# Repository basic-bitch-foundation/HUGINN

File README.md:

# HUGINN
 Introduction
--------------------------------------------
Huginn was crow of Odin (Greek God), He was messenger of hims. Thus this will be your personal messenger, let u communicate w/ hommies in any 9 realms.

It is a LoRa ( Long Range ) powered  pocket off grid pager.

## Build

It have BOM, Custom PCB, 3D printed Enclosure, buttons and suport.
Download All files(.stp) from Enclosure printable folder and print 'em
 > It uses M2 screw everywhere
 > For part link please download .odf not .csv
 > In assembly u may see the MCU as colliding with PCB dw! it just cz I can't remove the header pins. :lollll:

 ### Instructions
 First comes the MCU U hve to castellated solder it on top of the board or can use very low height header pins

 then Display as display I gave in BOM, Have 8 pin(Goes to HAT) to 8 , I will suggest to solder 'em direct , though half height n 2.54 header can use.
 
 Stating with solder all component On PCB ,
 As most part will be connected using wire to component to SMD solder Pad.
 1. Part u need to connect like this: ( Component--> wire--> Smd pad)
 > 5 switches
 >2 LEDs
 >Battery (optional)

 2. The semi rotating switch have two part one is switch with rod dropped and a pad
 put the switch inside carv and then fix the pad on left face of rod so i can press momentary switch.
 Then, Screw it from bellow (Enough clamp so that It can't move freely but can move!)

 3. As most part have support in Enclosure but gluing it make it smooth
 4. Glue the disc motor that will send vibration through body
 5. I don't gave the outing for LED cz It was ruining the Aesthetics of E ink's calm there so Any who want to see the charging status can place it nea usb input or a small hole behind panel

## Code
This is basic firmware code u can compile and flash it in MCU using Platform.io (a extension in VS code) or using Thonny (IDE)

## How to use it:
As pager need to be quick I added three code fn!
and a local converter:
So U navigate up/down 
between
143 ( I Love u!)
505 ( SOS )
etc.
the click the send button when reciver will reciver get it wil automaticall converted in their own device
. This save the bytes of daya is trasmitting and saving time 

# AI- decl.
I use like very little < 10% AI for code. 

# Outro
Made for Hackclub <3 by Saksham (A.K.A bbb)
Feel free to contribute :heart:

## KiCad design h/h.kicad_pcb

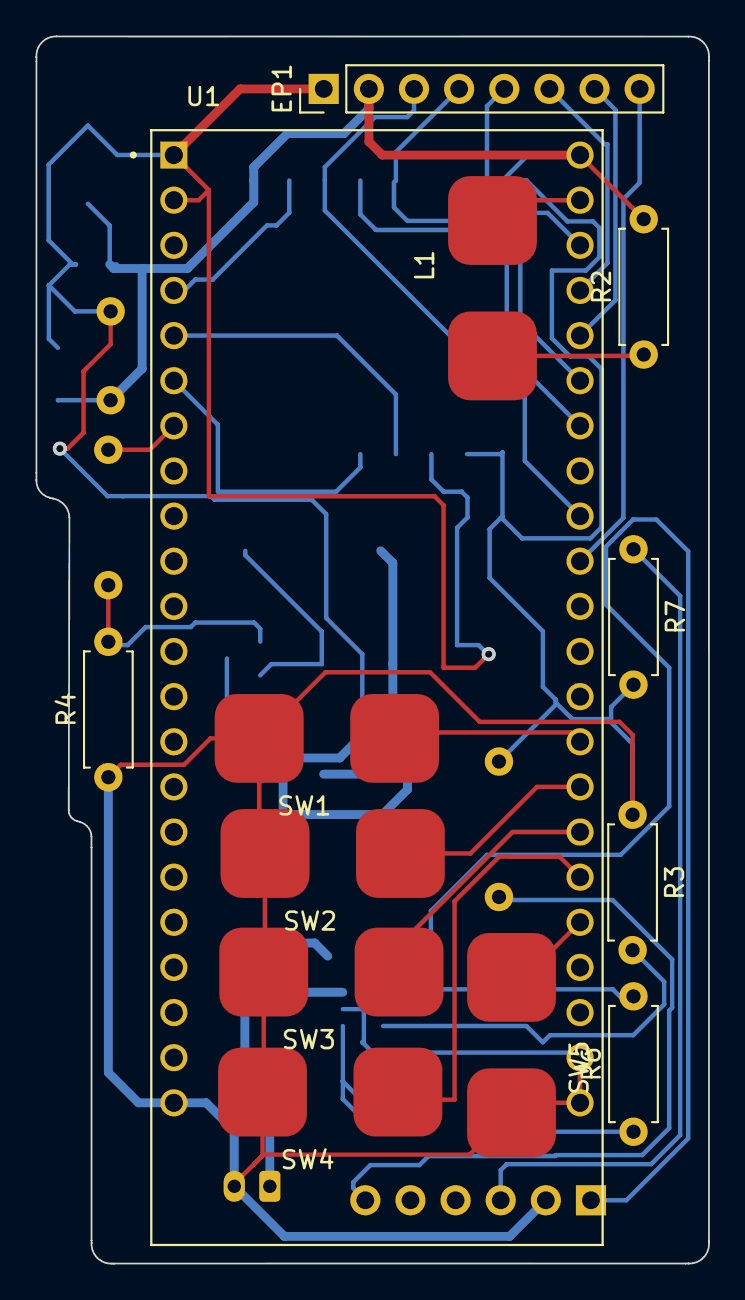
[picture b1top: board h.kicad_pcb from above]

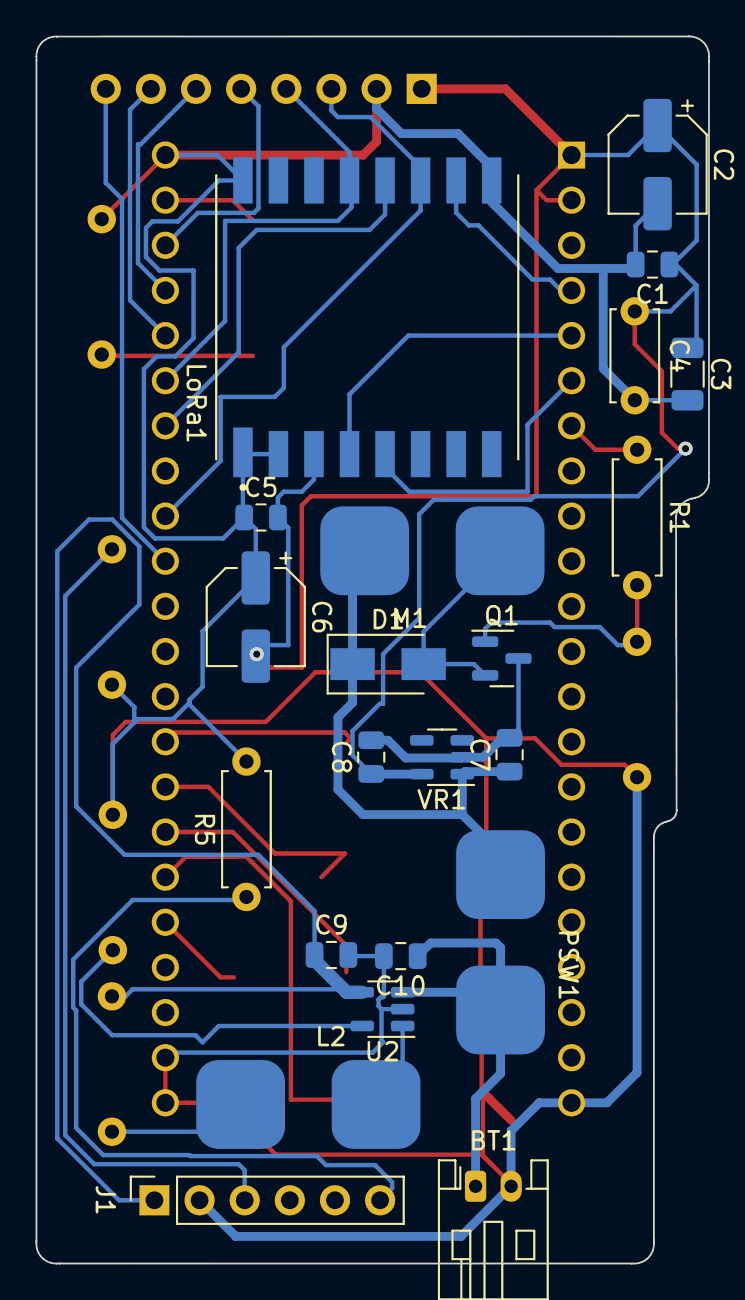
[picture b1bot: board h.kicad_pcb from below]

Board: 2 copper layers, 37.9 x 69.1 mm, 35 parts (22 on the bottom side), 28 nets.

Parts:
BT1: Battery; JST_PH_S2B-PH-K_1x02_P2.00mm_Horizontal
C1, C7, C8: 10uF; C_0805_2012Metric
C2, C6: 100uF; CP_Elec_5x5.3
C3: 47uF; C_1206_3216Metric
C4: 100nf; C_Disc_D5.0mm_W2.5mm_P5.00mm
C5: 10uf; C_0805_2012Metric
C9, C10: 4.7uF; C_0805_2012Metric
D1: D; D_SMA
EP1: display; PinHeader_1x08_P2.54mm_Vertical
J1: USB_C_Receptacle_USB2.0; PinSocket_1x06_P2.54mm_Vertical
L1, L2: LED; SolderWirePad_1x02_SMD_5x5mm
LoRa1: left; MODULE_RA-02_LORA
M1: Motor_DC; SolderWirePad_1x02_SMD_5x5mm
PSW1: SW_SPST; SolderWirePad_1x02_SMD_5x5mm
Q1: Q_NMOS_GDS; SOT-23
R1: 100Ω; R_Axial_DIN0207_L6.3mm_D2.5mm_P7.62mm_Horizontal
R2, R6: 1k; R_Axial_DIN0207_L6.3mm_D2.5mm_P7.62mm_Horizontal
R3: 2kΩ; R_Axial_DIN0207_L6.3mm_D2.5mm_P7.62mm_Horizontal
R4: 10k; R_Axial_DIN0207_L6.3mm_D2.5mm_P7.62mm_Horizontal
R5, R7: 5.1kΩ; R_Axial_DIN0207_L6.3mm_D2.5mm_P7.62mm_Horizontal
SW1: SW_L; SolderWirePad_1x02_SMD_5x5mm
SW2: SW_UP; SolderWirePad_1x02_SMD_5x5mm
SW3: SW_C; SolderWirePad_1x02_SMD_5x5mm
SW4: SW_DW; SolderWirePad_1x02_SMD_5x5mm
SW5: SW_R; SolderWirePad_1x02_SMD_5x5mm
U1: ESP32-S3-DEVKITC-1U-N8R8; ESP32-S3-DEVKITC-1-N8R8
U2: MCP73831-2-OT; SOT-23-5
VR1: AP2112K-3.3; SOT-23-5

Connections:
3V3: C1.1, C2.1, C3.1, C4.1, C5.2, C6.2, C8.1, EP1.1, LoRa1.3, U1.J1_1 (3V3), U1.J1_2 (3V3), VR1.5 (VOUT)
BAT_RAW: BT1.1, C10.1, PSW1.1 (A), U2.3 (VBAT)
BAT_SYS: C7.1, D1.1 (K), M1.1 (+), PSW1.2 (B), VR1.1 (VIN)
EP_BUSY: EP1.8, U1.J3_10 (GPIO38)
EP_CS: EP1.5, U1.J3_3 (U0RXD/GPIO44)
EP_DC: EP1.6, U1.J3_4 (GPIO1)
EP_RST: EP1.7, U1.J3_5 (GPIO2)
GATE: Q1.1 (G), R1.2, R4.2
GND: BT1.2, C1.2, C2.2, C3.2, C4.2, C5.1, C6.1, C7.2, C8.2, C9.2, C10.2, EP1.2, LoRa1.1, LoRa1.2, LoRa1.9, LoRa1.16, Q1.3 (S), R2.2, R3.1, R4.1, R5.2, R7.2, SW1.1 (A), SW2.1 (A), SW3.1 (A), SW4.1 (A), SW5.1 (A), U1.J1_22 (GND), U1.J3_1 (GND), U1.J3_21 (GND), U1.J3_22 (GND), U2.2 (VSS), VR1.2 (GND)
LORA_CS: LoRa1.10, U1.J1_4 (GPIO4)
LORA_DI00: LoRa1.5, U1.J1_6 (GPIO6)
LORA_RST: LoRa1.4, U1.J1_5 (GPIO5)
MC_VDD: C9.1, R6.2, U2.4 (VDD)
unnamed: D1.2 (A), M1.2 (-), Q1.2 (D)
unnamed: L1.2 (A), R2.1
unnamed: L2.1 (K), U2.1 (STAT)
unnamed: L2.2 (A), R6.1
unnamed: R1.1, U1.J1_7 (GPIO7)
unnamed: R3.2, U2.5 (PROG)
SPI_MISO: LoRa1.12, U1.J3_7 (MTDI/GPIO41)
SPI_MOSI: EP1.3, LoRa1.11, U1.J3_9 (MTCK/GPIO39)
SPI_SCK: EP1.4, LoRa1.13, U1.J3_6 (MTMS/GPIO42)
STS_LED: L1.1 (K), U1.J3_2 (U0TXD/GPIO43)
SW_C: SW3.2 (B), U1.J3_16 (GPIO48)
SW_DW: SW4.2 (B), U1.J3_17 (GPIO47)
SW_L: SW1.2 (B), U1.J3_14 (GPIO0)
SW_R: SW5.2 (B), U1.J3_18 (GPIO21)
SW_UP: SW2.2 (B), U1.J3_15 (GPIO45)

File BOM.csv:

Reference,Qty,Category,Component,Value,Manufacturer,Part Number / Model,Package / Footprint,Description,Supplier Link,Price (USD),Price (INR),Notes
U1,1,Microcontrollers,ESP32-S3 Dev Board,N8R8,Espressif,ESP32-S3-DEVKITC-1-N8R8,DEVKITC-1U (castellated module),ESP32-S3 Development Board (8MB Flash / 8MB PSRAM),here,,1304.1,Used as system module - not a bare SoC
LoRa1,1,RF Modules,LoRa Transceiver Module,433MHz,Ai-Thinker,RA-02 (SX1278),SMD Module - 16 pin (2x8 top/bottom),433 MHz LoRa Transceiver Module (SX1278-based),here,,301,Confirm 433 MHz vs 868/915 MHz variant needed for your region
VR1,1,Power Management,LDO Voltage Regulator,3.3V,Diodes Inc.,AP2112K-3.3,SOT-23-5,3.3V 600mA Low Dropout Voltage Regulator,here,,26,
U2,1,Power Management,LiPo Charge Controller IC,-,Microchip,MCP73831T-2ACI/OT,SOT-23-5,Single-Cell Li-Po/Li-Ion Linear Charge Management IC,here,,71.83,
J1,1,Connectors,USB Type-C Receptacle,-,,,SMD Type-C 16-pin,USB Type-C Power/Data Connector (USB 2.0),here,,34,different from footprint
BT1,1,Connectors,Battery Connector,2-pin,JST,PH-2 (S2B-PH-K),JST-PH 2.00mm 2-pin Horizontal,JST-PH 2-Pin Battery Connector,here,,8,Can skip very optional
EP1,1,Connectors,E-Ink Display Connector,8-pin,Generic,PinHeader-1x08-2.54mm,2.54mm Pitch 1x08 Vertical Header,"2.13"" SPI E-Ink Display Header (8-pin)",here,,1478,
PSW1,1,Switches,Momentary switch,Power,Generic,,SMD 2-pin,,here,,39,
SW1,1,Switches,Tactile Push Button,Left,Generic,Tactile SMD 2-pin,SolderPad 5x5mm SMD,Tactile Push Button (Left / Navigation),here,,1.05,
SW2,1,Switches,Tactile Push Button,Up,Generic,Tactile SMD 2-pin,SolderPad 5x5mm SMD,Tactile Push Button (Up / Navigation),"""",,,
SW3,1,Switches,Tactile Push Button,Send,Generic,Tactile SMD 2-pin,SolderPad 5x5mm SMD,Tactile Push Button (Center / Select),"""",,,
SW4,1,Switches,Tactile Push Button,Down,Generic,Tactile SMD 2-pin,SolderPad 5x5mm SMD,Tactile Push Button (Down / Navigation),"""",,,
SW5,1,Switches,Tactile Push Button,Right,Generic,Tactile SMD 2-pin,SolderPad 5x5mm SMD,Momentary Tactile Push Button (Right / Navigation),here,,,
L1,1,LEDs,Status LED,diode led,Generic,LED-0805,SolderPad 5x5mm SMD,Status Indicator LED,,,,
L2,1,LEDs,Charge Status LED,"""",Generic,LED-0805,SolderPad 5x5mm SMD,Battery Charge Status LED,,,,
Q1,1,Transistors,N-Channel MOSFET,-,Generic,BSS138,SOT-23,N-Channel MOSFET (Motor Driver Switch),here,,2.02,
D1,1,Diodes,Flyback/Protection Diode,-,Generic,1N4148 or equiv.,SMA,Diode (Motor Flyback Protection),,,,
R1,1,Resistors,Resistor,100?,Generic,RC-Series,Axial THT (DIN0207),100? Resistor (LoRa Reset Gate),,,,
R2,1,Resistors,Resistor,1k?,Generic,RC-Series,Axial THT (DIN0207),1k? Resistor (Status LED Current Limit),,,,regional prices and availiblity varries
R3,1,Resistors,Resistor,2k?,Generic,RC-Series,Axial THT (DIN0207),2k? Resistor (Charge IC PROG - Sets Charge Current),,,,regional prices and availiblity varries
R4,1,Resistors,Resistor,10k?,Generic,RC-Series,Axial THT (DIN0207),10k? Resistor (MOSFET Gate Pulldown),,,,regional prices and availiblity varries
R5,1,Resistors,Resistor,5.1k?,Generic,RC-Series,Axial THT (DIN0207),5.1k? Resistor (USB-C CC1 Pull-down),,,,regional prices and availiblity varries
R6,1,Resistors,Resistor,1k?,Generic,RC-Series,Axial THT (DIN0207),1k? Resistor (Charge LED Current Limit),,,,
R7,1,Resistors,Resistor,5.1k?,Generic,RC-Series,Axial THT (DIN0207),5.1k? Resistor (USB-C CC2 Pull-down),,,,
C1,1,Capacitors,Capacitor,10uF,Generic,C-Series,0805 SMD,10uF Ceramic Capacitor (E-Ink Supply Decoupling),,,,
C2,1,Capacitors,Capacitor,100uF,Generic,CP-Elec,5x5.3mm Electrolytic,100uF Electrolytic Capacitor (E-Ink Bulk Decoupling),,,,
C3,1,Capacitors,Capacitor,47uF,Generic,C-Series,1206 SMD,47uF Capacitor (ESP32 Supply Decoupling),,,,
C4,1,Capacitors,Capacitor,100nF,Generic,C-Disc,THT Disc 5mm,100nF Capacitor (ESP32 Supply Decoupling),,,,
C5,1,Capacitors,Capacitor,10uF,Generic,C-Series,0805 SMD,10uF Capacitor (LoRa Module Supply Decoupling),,,,
C6,1,Capacitors,Capacitor,100uF,Generic,CP-Elec,5x5.3mm Electrolytic,100uF Electrolytic Capacitor (LoRa Module Bulk Decoupling),,,,
C7,1,Capacitors,Capacitor,10uF,Generic,C-Series,0805 SMD,10uF Capacitor (LDO Input Decoupling),,,,
C8,1,Capacitors,Capacitor,10uF,Generic,C-Series,0805 SMD,10uF Capacitor (LDO Output Decoupling),,,,
C9,1,Capacitors,Capacitor,4.7uF,Generic,C-Series,0805 SMD,4.7uF Capacitor (Charge IC VDD Decoupling),,,,
C10,1,Capacitors,Capacitor,4.7uF,Generic,C-Series,0805 SMD,4.7uF Capacitor (Charge IC VBAT Decoupling),,,,""""
M1,1,Motors,Coin Vibration Motor,-,Generic,Coin Vibe 10mm,SolderPad 5x5mm SMD,Coin Vibration Motor (Haptic Feedback),here,,73,
,,,,,,,,,,,,
,,,,,,,,,,TOTAL = ,~3500,

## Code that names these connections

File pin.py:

lora_cs = 4
lora_rst = 5
lora_d0 = 7

spi_sck = 42
spi_miso = 41
spi_mosi = 39

ep_cs = 44
ep_dc = 1
ep_rst = 2
ep_bsy = 40

sw_l = 0
sw_up = 45
sw_c = 48
sw_dw = 47
sw_r = 21
sts_led = 43
mtr_gt = 6

fsfmnjgs
oprtyh

n4366538
566

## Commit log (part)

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2026-06-27 check desc/
    -completed schematics
    -PCB design and routing
    -sanity check
    -ERC / DRC checked
2026-06-30 Check desc.
    many things
    in devlog
    in short
    added button
    it support
    power button design
